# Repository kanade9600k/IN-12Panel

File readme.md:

# IN-12PANEL

## 概要

* ニキシー管4桁をダイナミック点灯させるための基板
* 4管の桁表示線をつないでアノード線を分けただけのもの
* 制御は他の基板で行う

## 回路図

## 外観

* 表

* 裏

## その他

一応手元で動きましたが，動作保証はできません

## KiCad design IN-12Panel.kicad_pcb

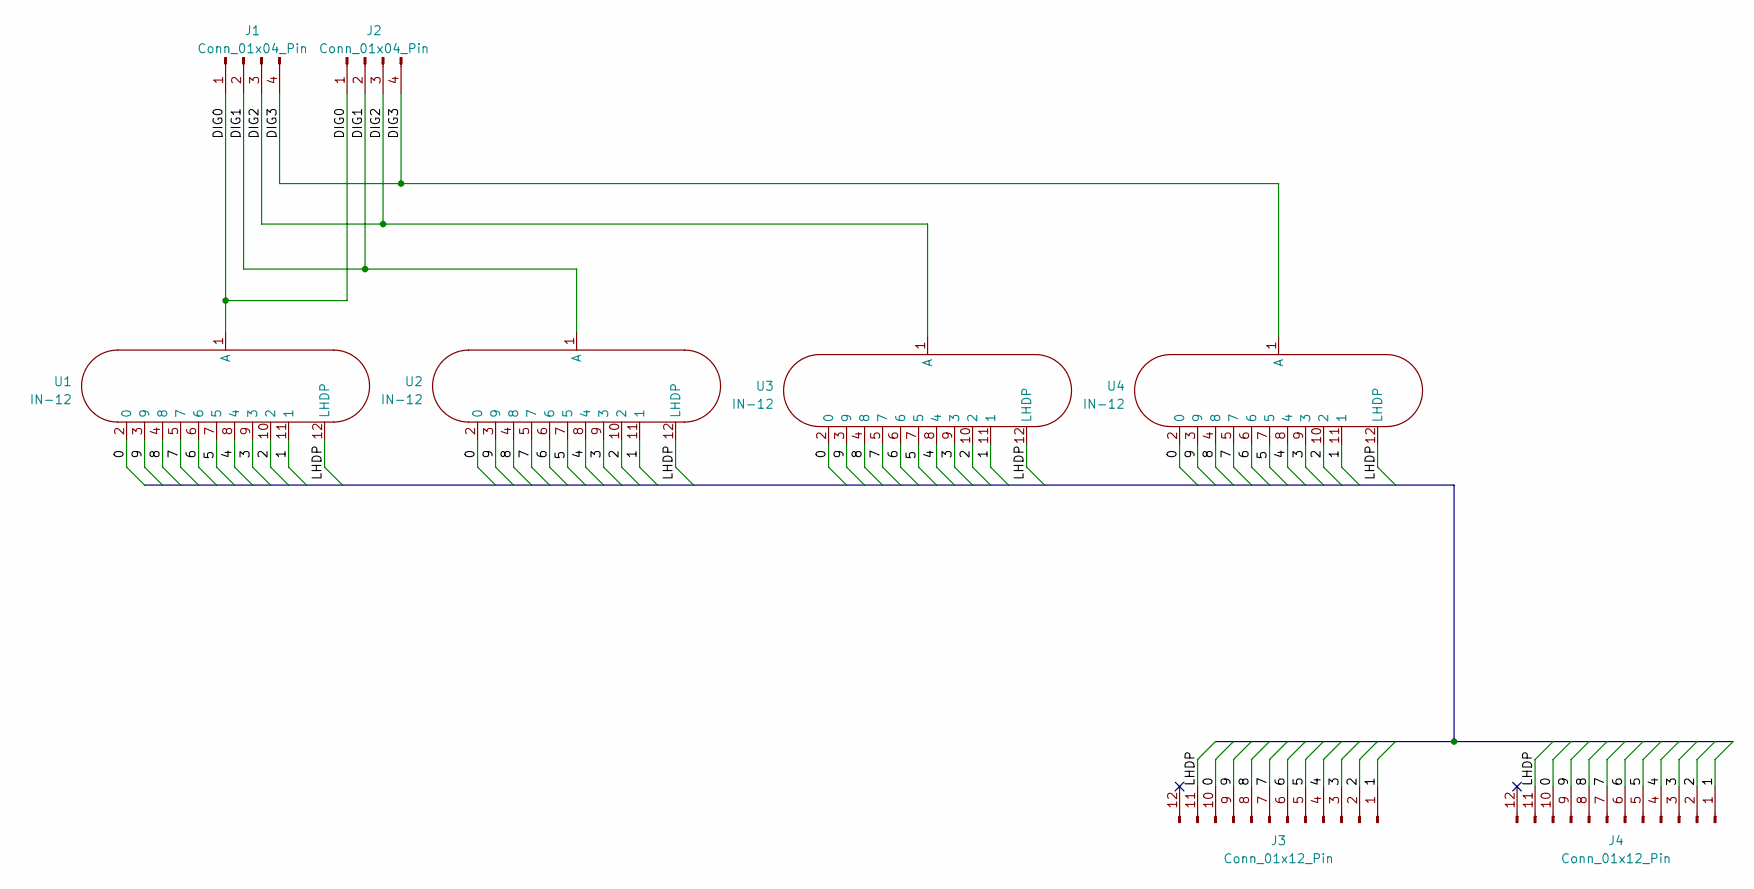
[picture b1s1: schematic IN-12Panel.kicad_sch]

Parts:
J1, J2: Conn_01x04_Pin; JST_XH_S4B-XH-A_1x04_P2.50mm_Horizontal
J3, J4: Conn_01x12_Pin; JST_XH_S12B-XH-A_1x12_P2.50mm_Horizontal
U1, U2, U3, U4: IN-12; nixies-IN-12

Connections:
/0: J3.10, J4.10, U1.2 (0), U2.2 (0), U3.2 (0), U4.2 (0)
/1: J3.1, J4.1, U1.11 (1), U2.11 (1), U3.11 (1), U4.11 (1)
/2: J3.2, J4.2, U1.10 (2), U2.10 (2), U3.10 (2), U4.10 (2)
/3: J3.3, J4.3, U1.9 (3), U2.9 (3), U3.9 (3), U4.9 (3)
/4: J3.4, J4.4, U1.8 (4), U2.8 (4), U3.8 (4), U4.8 (4)
/5: J3.5, J4.5, U1.7 (5), U2.7 (5), U3.7 (5), U4.7 (5)
/6: J3.6, J4.6, U1.6, U2.6, U3.6, U4.6
/7: J3.7, J4.7, U1.5 (7), U2.5 (7), U3.5 (7), U4.5 (7)
/8: J3.8, J4.8, U1.4 (8), U2.4 (8), U3.4 (8), U4.4 (8)
/9: J3.9, J4.9, U1.3 (9), U2.3 (9), U3.3 (9), U4.3 (9)
/DIG0: J1.1, J2.1, U1.1 (A)
/DIG1: J1.2, J2.2, U2.1 (A)
/DIG2: J1.3, J2.3, U3.1 (A)
/DIG3: J1.4, J2.4, U4.1 (A)
/LHDP: J3.11, J4.11, U1.12 (LHDP), U2.12 (LHDP), U3.12 (LHDP), U4.12 (LHDP)

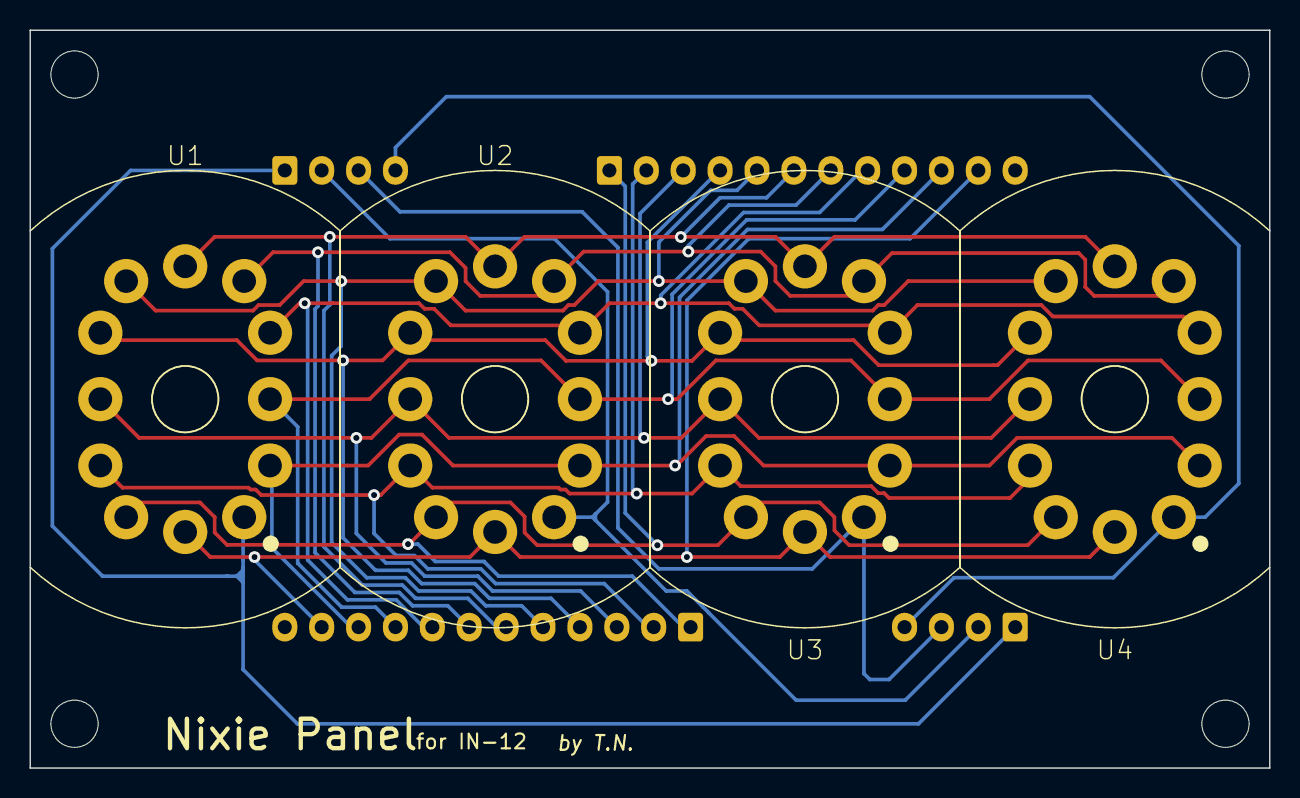
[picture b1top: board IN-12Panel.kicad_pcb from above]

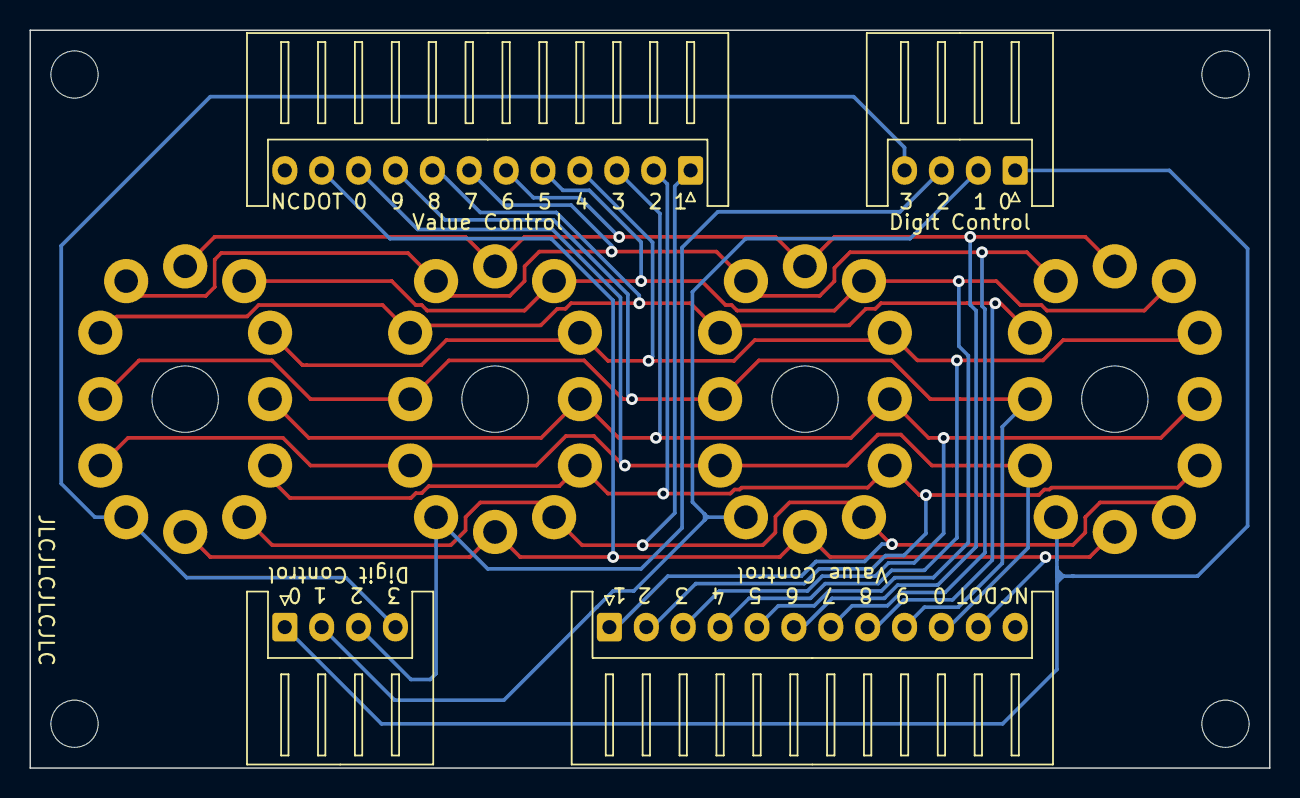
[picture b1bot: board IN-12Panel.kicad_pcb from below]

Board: 2 copper layers, 84.0 x 50.0 mm, 8 parts (4 on the bottom side), 15 nets.

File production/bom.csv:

Designator,Footprint,Quantity,Value,LCSC Part #
"J1, J2",JST_XH_S4B-XH-A_1x04_P2.50mm_Horizontal,2,Conn_01x04_Pin,
"J3, J4",JST_XH_S12B-XH-A_1x12_P2.50mm_Horizontal,2,Conn_01x12_Pin,
"U1, U2, U3, U4",nixies-IN-12,4,IN-12,

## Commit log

2023-03-17 最初のコミット
2023-03-17 配置を完了
2023-03-21 基板結合にあたり，コネクタの位置・向きを変更
2023-05-27 製造後データを追加
2023-05-27 readmeを追加
2023-05-27 readmeに基板画像を追加
